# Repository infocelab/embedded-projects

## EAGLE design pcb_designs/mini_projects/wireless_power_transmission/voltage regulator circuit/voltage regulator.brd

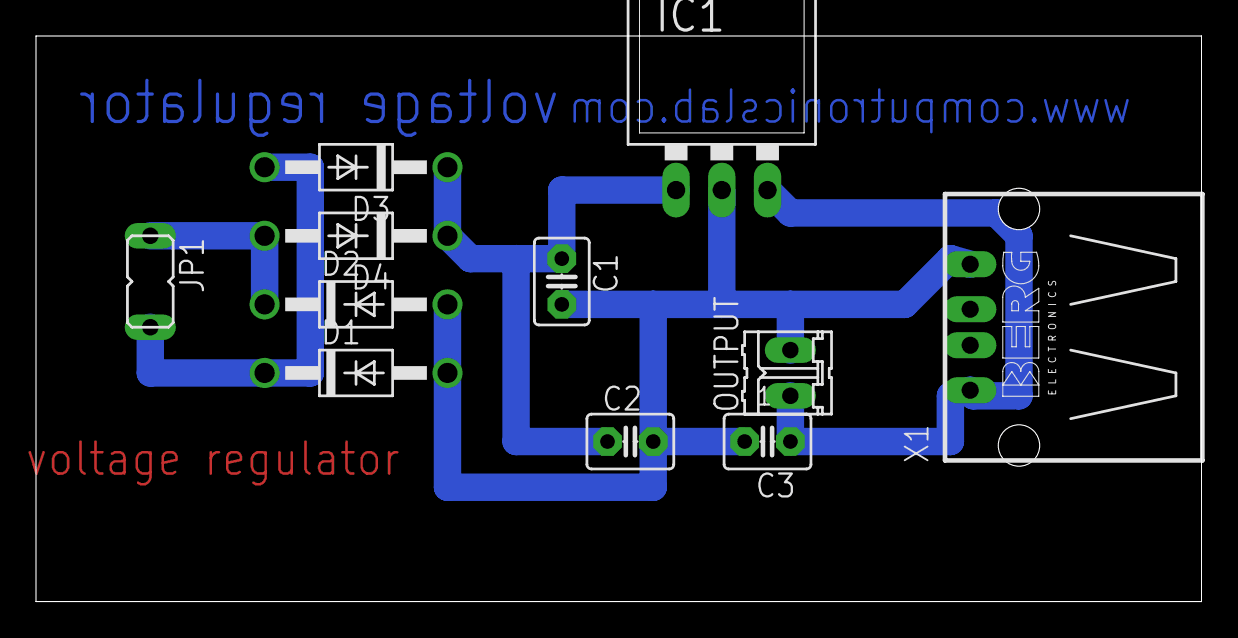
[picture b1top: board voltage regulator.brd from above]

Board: 2 copper layers, 64.8 x 31.4 mm, 11 parts (0 on the bottom side), 5 nets.

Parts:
C1: 47uf; C2.5-3
C2, C3: 0.1uf; C2.5-3
D1, D2, D3, D4: 1N4007; DO41-10
IC1: 7805; 78XXL
JP1: transformer; JP1
OUTPUT: 02P
X1: PN87520

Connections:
unnamed: C1.2, C2.2, C3.2, D1.A, D2.A, IC1.GND, OUTPUT.2, X1.4
unnamed: C1.1, C2.1, D3.C, D4.C, IC1.IN
unnamed: D2.C, D4.A, JP1.1
unnamed: D1.C, D3.A, JP1.2
unnamed: C3.1, IC1.OUT, OUTPUT.1, X1.1

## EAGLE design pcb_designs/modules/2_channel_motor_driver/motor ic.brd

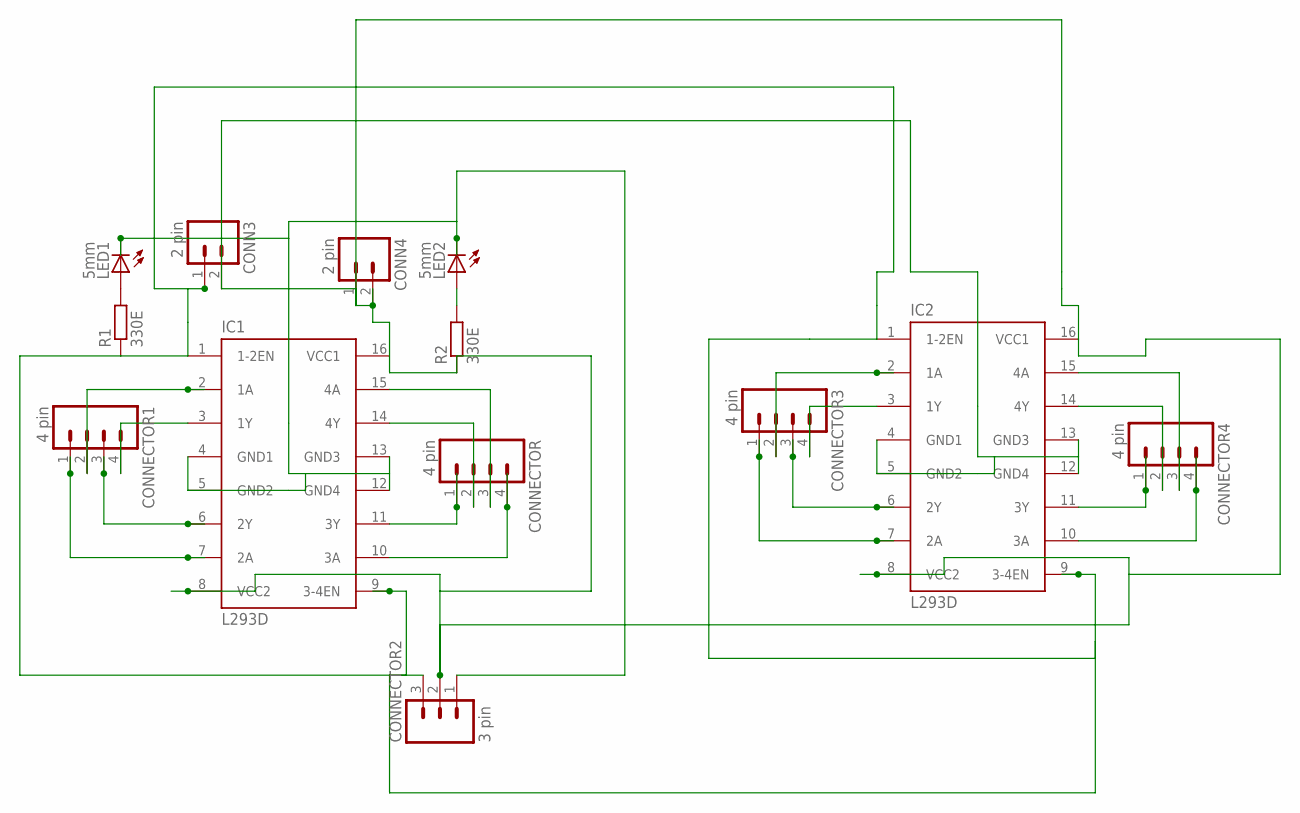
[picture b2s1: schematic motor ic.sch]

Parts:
CONN3, CONN4: 2 pin; 02P
CONNECTOR, CONNECTOR1, CONNECTOR3, CONNECTOR4: 4 pin; 04P
CONNECTOR2: 3 pin; 03P
IC1, IC2: L293D; DIL16
LED1, LED2: 5mm; LED_LD260
R1, R2: 330E; 0204/7

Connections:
unnamed: LED1.A, R1.2
unnamed: LED2.A, R2.2
unnamed: CONNECTOR1.2, IC1.2 (1A)
unnamed: CONNECTOR1.4, IC1.3 (1Y)
unnamed: CONNECTOR1.3, IC1.6 (2Y)
unnamed: CONNECTOR1.1, IC1.7 (2A)
unnamed: CONNECTOR.3, IC1.15 (4A)
unnamed: CONNECTOR.4, IC1.10 (3A)
unnamed: CONNECTOR.2, IC1.14 (4Y)
unnamed: CONNECTOR.1, IC1.11 (3Y)
unnamed: CONN3.2, CONN4.1, CONNECTOR2.1, IC1.4 (GND1), IC1.5 (GND2), IC1.12 (GND4), IC1.13 (GND3), IC2.4 (GND1), IC2.5 (GND2), IC2.12 (GND4), IC2.13 (GND3), LED1.K (C), LED2.K (C)
unnamed: CONN3.1, CONNECTOR2.3, IC1.1 (1-2EN), IC1.9 (3-4EN), IC2.1 (1-2EN), IC2.9 (3-4EN), R1.1
unnamed: CONN4.2, CONNECTOR2.2, IC1.8 (VCC2), IC1.16 (VCC1), IC2.8 (VCC2), IC2.16 (VCC1), R2.1
unnamed: CONNECTOR3.2, IC2.2 (1A)
unnamed: CONNECTOR3.4, IC2.3 (1Y)
unnamed: CONNECTOR3.3, IC2.6 (2Y)
unnamed: CONNECTOR3.1, IC2.7 (2A)
unnamed: CONNECTOR4.3, IC2.15 (4A)
unnamed: CONNECTOR4.4, IC2.10 (3A)
unnamed: CONNECTOR4.2, IC2.14 (4Y)
unnamed: CONNECTOR4.1, IC2.11 (3Y)

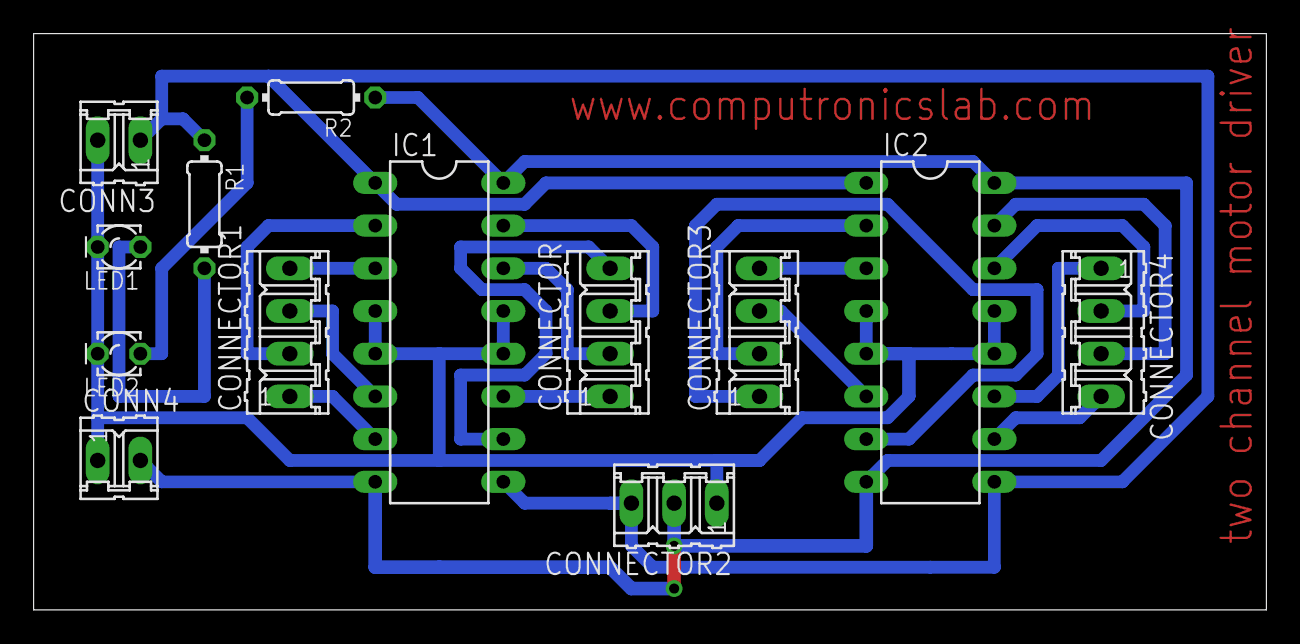
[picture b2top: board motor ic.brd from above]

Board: 2 copper layers, 73.3 x 34.3 mm, 13 parts (0 on the bottom side), 21 nets.

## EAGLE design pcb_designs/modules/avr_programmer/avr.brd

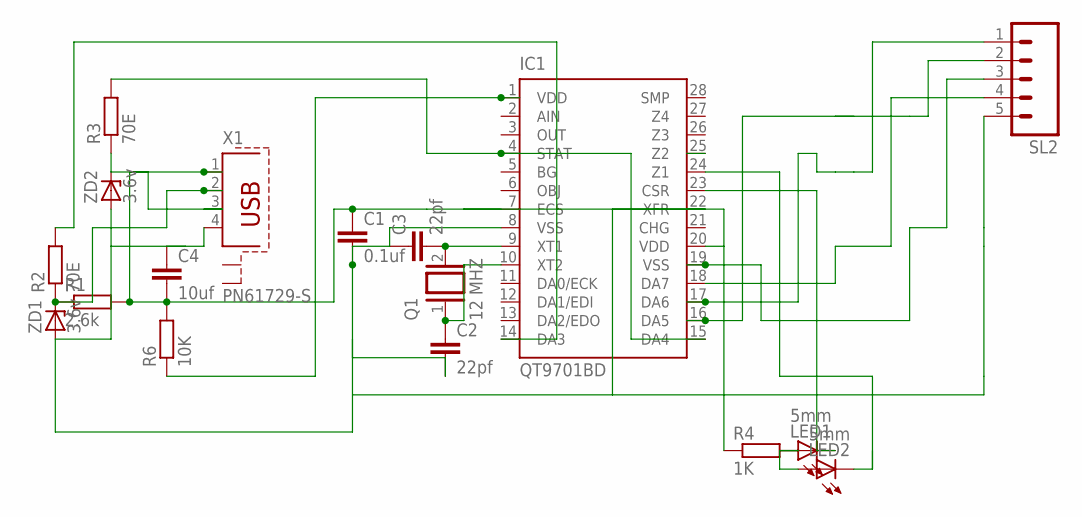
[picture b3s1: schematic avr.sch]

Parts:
C1: 0.1uf; C2.5-3
C2, C3: 22pf; C2.5-3
C4: 10uf; C2.5-3
IC1: QT9701BD; DIL28-3
LED1, LED2: 5mm; LED3MM
Q1: 12 MHZ; QS
R1: 2.6k; 0204/7
R2, R3: 70E; 0204/7
R4: 1K; 0204/7
R6: 10K; 0204/7
SL2: M05; 05P
X1: PN61729-S
ZD1, ZD2: 3.6v; SOD81

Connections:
unnamed: C3.2, IC1.9 (XT1), Q1.2
unnamed: C2.1, IC1.10 (XT2), Q1.1
unnamed: IC1.1 (VDD), R6.1
unnamed: R1.1, R2.1, X1.2, ZD1.C
unnamed: C1.2, C2.2, C3.1, C4.1, IC1.8 (VSS), IC1.22 (XFR), SL2.5, X1.4, ZD1.A, ZD2.A
unnamed: IC1.14 (DA3), R2.2
unnamed: R3.1, X1.3, ZD2.C
unnamed: IC1.4 (STAT), IC1.15 (DA4), R3.2
unnamed: C1.1, C4.2, IC1.7 (ECS), IC1.20 (VDD), R1.2, R4.1, R6.2, X1.1
unnamed: IC1.24 (Z1), LED2.K (C)
unnamed: IC1.23 (CSR), LED1.K (C)
unnamed: IC1.17 (DA6), SL2.1
unnamed: IC1.16 (DA5), SL2.2
unnamed: IC1.19 (VSS), SL2.3
unnamed: IC1.18 (DA7), SL2.4
unnamed: LED1.A, LED2.A, R4.2

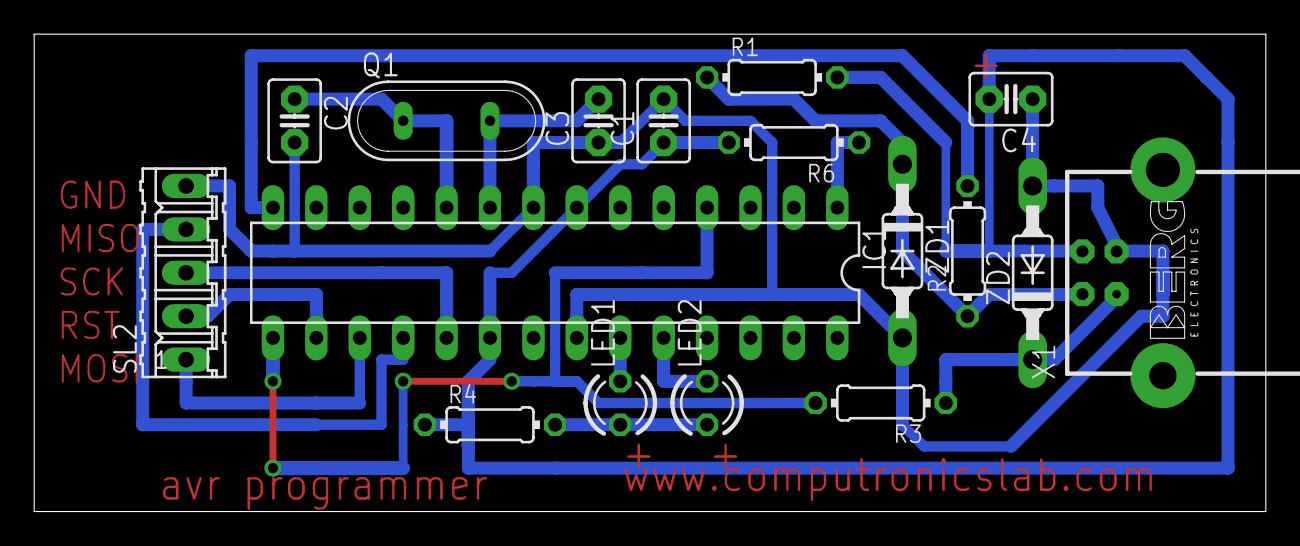
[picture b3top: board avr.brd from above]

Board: 2 copper layers, 72.1 x 27.9 mm, 17 parts (0 on the bottom side), 16 nets.

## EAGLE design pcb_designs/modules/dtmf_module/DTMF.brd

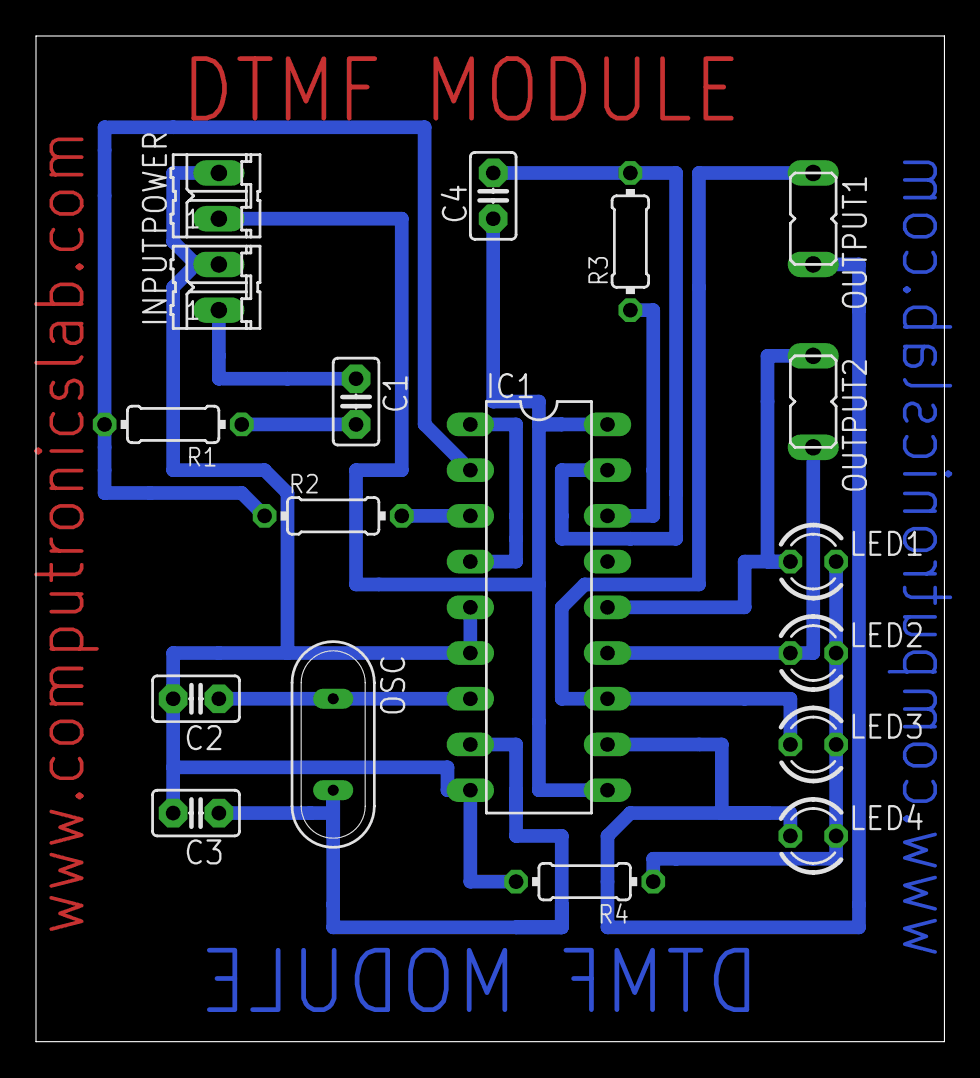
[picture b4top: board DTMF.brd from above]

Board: 2 copper layers, 50.5 x 55.9 mm, 18 parts (0 on the bottom side), 16 nets.

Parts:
C1: 0.1uf; C2.5-2
C2, C3: 22PF; C2.5-2
C4: 0.1UF; C2.5-2
IC1: CM8870CP; DIL18
INPUT: 02P
LED1, LED2, LED3, LED4: 3mm; LED3MM
OSC: 3.57; QS
OUTPUT1, OUTPUT2: JP1
POWER: 02P
R1: 10K; 0204/7
R2, R3: 100K; 0204/7
R4: 330E; 0204/7

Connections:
unnamed: C2.2, C3.2, IC1.5, IC1.6, IC1.9, INPUT.2, POWER.2, R4.2
unnamed: C1.2, R1.1
unnamed: IC1.3, R2.2
unnamed: LED1.K, LED2.K, LED3.K, LED4.K, R4.1
unnamed: IC1.11, LED4.A, OUTPUT1.2
unnamed: IC1.12, LED3.A, OUTPUT1.1
unnamed: IC1.13, LED2.A, OUTPUT2.2
unnamed: IC1.14, LED1.A, OUTPUT2.1
unnamed: C4.1, IC1.10, IC1.18, POWER.1
unnamed: C1.1, INPUT.1
unnamed: IC1.2, R1.2, R2.1
unnamed: IC1.1, IC1.4
unnamed: C2.1, IC1.7, OSC.1
unnamed: C3.1, IC1.8, OSC.2
unnamed: IC1.16, R3.1
unnamed: C4.2, IC1.17, R3.2

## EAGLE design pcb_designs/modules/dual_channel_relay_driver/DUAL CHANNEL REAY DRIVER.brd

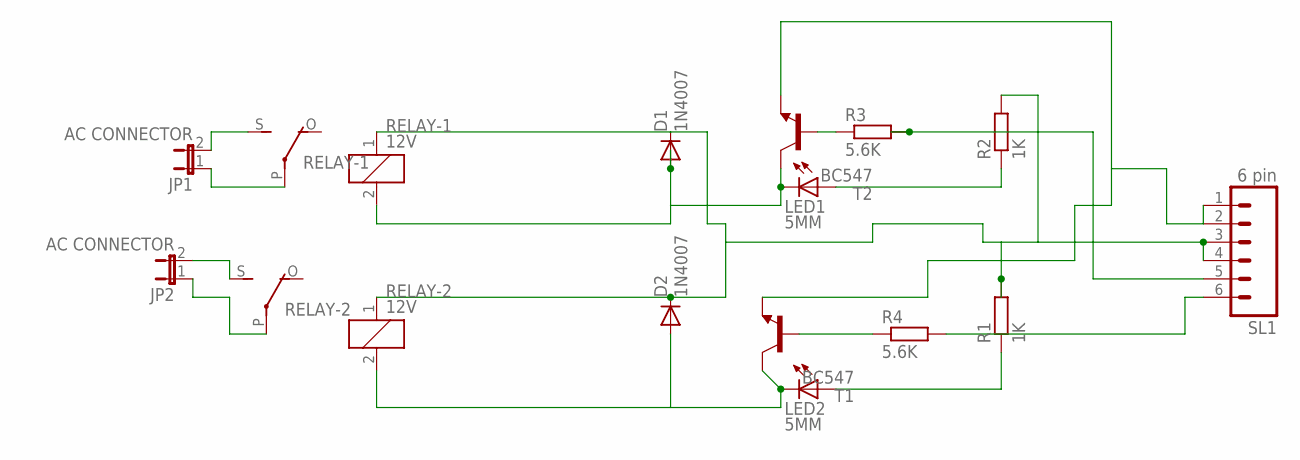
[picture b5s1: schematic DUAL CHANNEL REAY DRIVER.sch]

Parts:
D1, D2: 1N4007; DO41-10
JP1, JP2: AC CONNECTOR; JP1
LED1, LED2: 5MM; LED5MM
R1, R2: 1K; 0204/7
R3, R4: 5.6K; 0204/7
RELAY-1, RELAY-2: 12V; G5LE
SL1: 6 pin; 06P
T1, T2: BC547; TO92

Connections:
unnamed: D1.A, LED1.K (C), RELAY-1.2, T2.3 (C)
unnamed: D1.C, D2.C, R1.2, R2.2, RELAY-1.1, RELAY-2.1, SL1.3, SL1.4
unnamed: JP2.2, RELAY-2.S
unnamed: R4.1, T1.2 (B)
unnamed: R3.1, T2.2 (B)
unnamed: LED1.A, R2.1
unnamed: LED2.A, R1.1
unnamed: JP1.2, RELAY-1.S
unnamed: JP1.1, RELAY-1.P
unnamed: JP2.1, RELAY-2.P
unnamed: SL1.1, SL1.2, T1.1 (E), T2.1 (E)
unnamed: R3.2, SL1.5
unnamed: R4.2, SL1.6
unnamed: D2.A, LED2.K (C), RELAY-2.2, T1.3 (C)

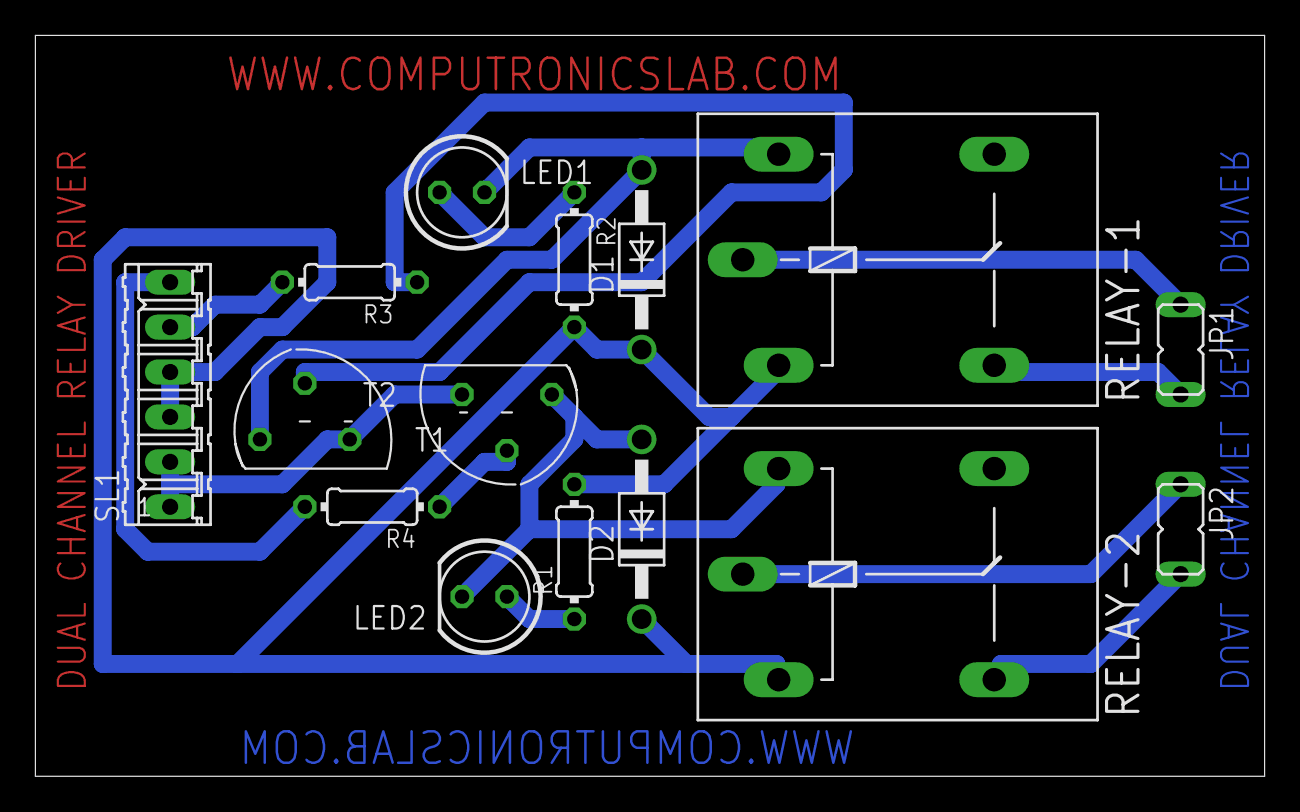
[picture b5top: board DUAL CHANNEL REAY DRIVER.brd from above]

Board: 2 copper layers, 69.5 x 41.9 mm, 15 parts (0 on the bottom side), 14 nets.

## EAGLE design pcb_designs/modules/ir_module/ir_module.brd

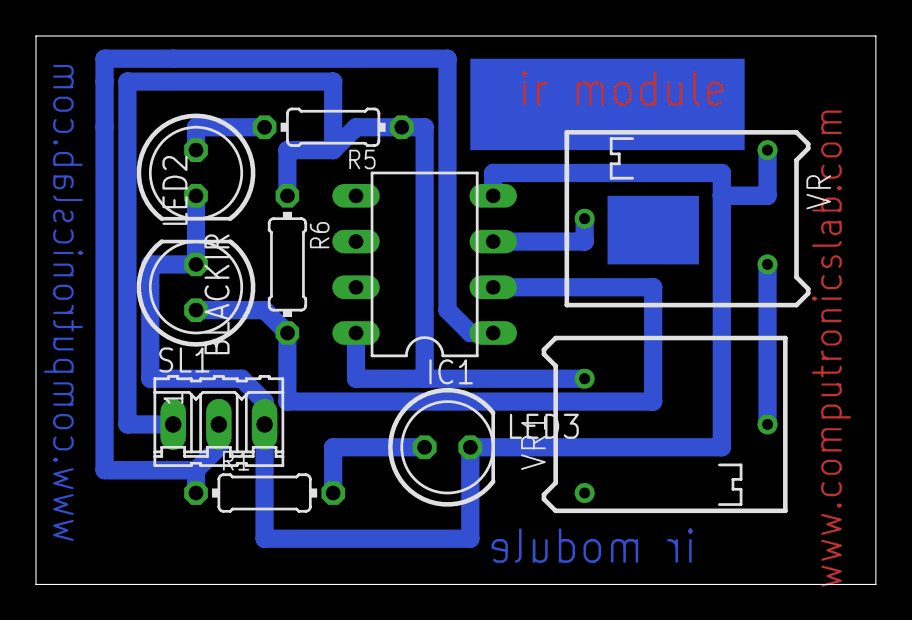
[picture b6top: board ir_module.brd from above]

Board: 2 copper layers, 46.7 x 30.5 mm, 10 parts (0 on the bottom side), 8 nets.

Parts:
BLACKIR: 5mm; LED5MM
IC1: 358; DIL-08
LED2, LED3: 5mm; LED5MM
R1, R5: 1K; 0204/7
R6: 10K; 0204/7
SL1: 03P
VR: 50k; RTRIM64P
VR1: 100E; RTRIM64P

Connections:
unnamed: IC1.8, R5.1, R6.1, SL1.1, VR1.3
unnamed: IC1.1, R1.1, SL1.2
unnamed: LED3.A, R1.2
unnamed: BLACKIR.A, R5.2
unnamed: IC1.3, VR.2
unnamed: IC1.2, LED2.A, R6.2
unnamed: VR.3, VR1.2
unnamed: BLACKIR.K, IC1.4, LED2.K, LED3.K, SL1.3, VR.1

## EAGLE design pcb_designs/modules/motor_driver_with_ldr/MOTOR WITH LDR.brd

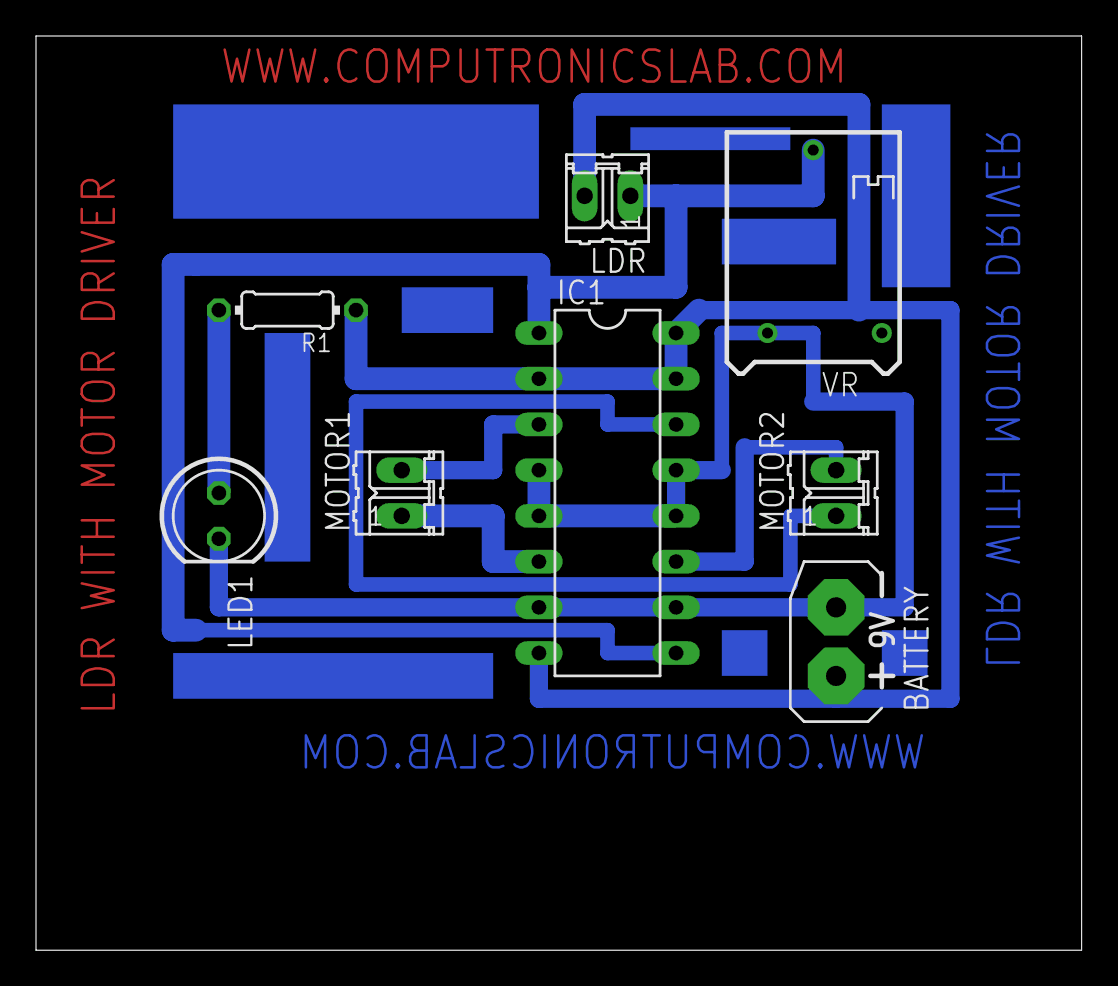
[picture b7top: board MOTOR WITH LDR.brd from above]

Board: 2 copper layers, 58.1 x 50.8 mm, 8 parts (0 on the bottom side), 8 nets.

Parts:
BATTERY: 9V; AB9V
IC1: L293D; DIL16
LDR: 02P
LED1: 5MM; LED5MM
MOTOR1, MOTOR2: 02P
R1: 330E; 0204/7
VR: 20K; RTRIM64P

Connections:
unnamed: IC1.14, MOTOR2.1
unnamed: IC1.11, MOTOR2.2
unnamed: LED1.A, R1.2
unnamed: BATTERY.+, IC1.2, IC1.8, IC1.15, IC1.16, LDR.2, R1.1
unnamed: BATTERY.-, IC1.4, IC1.5, IC1.7, IC1.10, IC1.12, IC1.13, LED1.K, VR.3
unnamed: IC1.1, IC1.9, LDR.1, VR.2
unnamed: IC1.6, MOTOR1.1
unnamed: IC1.3, MOTOR1.2
